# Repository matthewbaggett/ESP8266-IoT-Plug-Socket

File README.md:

ESP8266 IoT Plug Socket
=======================

This is a drop-in-replacement board for the STATUS Model RCS-K09 radio-controlled wallplug.
This allows you to insert an ESP8266 into a wallplug and use it as an Internet-of-Things controllable device.

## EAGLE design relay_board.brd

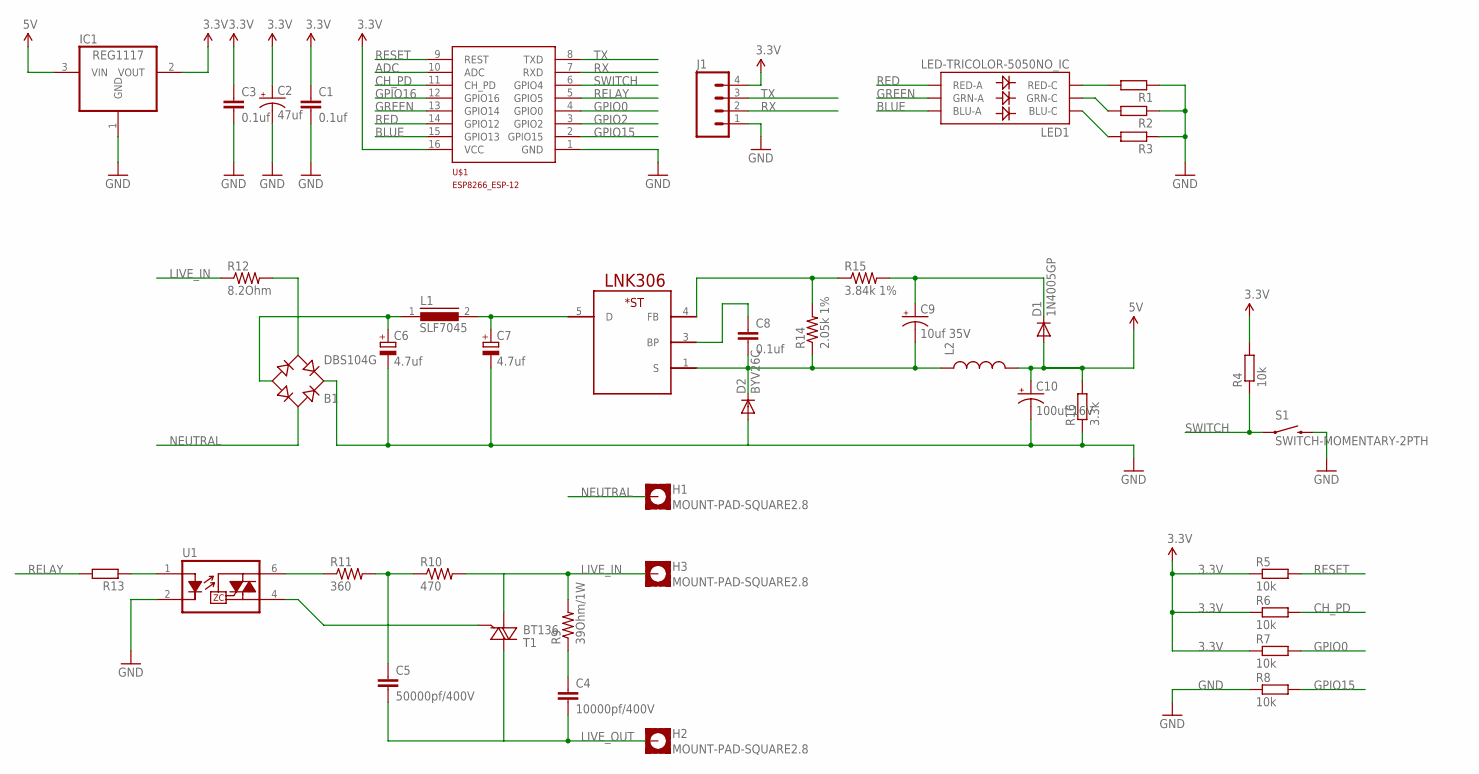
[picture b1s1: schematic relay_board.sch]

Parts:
B1: DBS104G; DBS
C1, C3: 0.1uf; 0805
C2: 47uf; PANASONIC_E
C4: 10000pf/400V; C050-045X075
C5: 50000pf/400V; C150-072X183
C6, C7: 4.7uf; E3,5-10
C8: 0.1uf; CAP-PTH-SMALL-KIT
C9: 10uf 35V; CPOL-RADIAL-10UF-25V-KIT
C10: 100uf 16V; CPOL-RADIAL-100UF-25V
D1: 1N4005GP; DO41-10
D2: BYV26C; SOD57-10
DA1: LNK306LNK306; LNK306_SMB
H1, H2, H3: MOUNT-PAD-SQUARE2.8; 2,8-PAD-SQUARE
IC1: REG1117; SOT223
J1: M04LOCK; 1X04_LOCK
L1: SLF7045
L2: INDUCTORDR1030; DR1030
LED1: LED-TRICOLOR-5050NO_IC; LED-TRICOLOR-5050
R1, R2, R3, R13: R-EU_M0805; M0805
R4: 10k; M0805
R5, R6, R7, R8: 10k; R0805
R9: 39Ohm/1W; AXIAL-0.6
R10: 470; AXIAL-0.4
R11: 360; AXIAL-0.4
R12: 8.2Ohm; AXIAL-0.6
R14: 2.05k 1%; 0805
R15: 3.84k 1%; 0805
R16: 3.3k; M0805
S1: SWITCH-MOMENTARY-2PTH; TACTILE-PTH
T1: BT136; TO220AB
U1: MOC3063S; DIP8SMD
U$1: ESP8266_ESP-12; ESP8266-ESP12

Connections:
3.3V: C1.1, C2.+, C3.1, IC1.2 (VOUT), J1.4, R4.2, R5.1, R6.1, R7.1, U$1.16 (VCC)
5V: C10.1 (+), D1.A, IC1.3 (VIN), L2.2, R16.2
ADC: U$1.10 (ADC)
BLUE: LED1.3 (BLU-A), U$1.15 (GPIO13)
CH_PD: R6.2, U$1.11 (CH_PD)
GND: B1.+, C1.2, C2.-, C3.2, C6.-, C7.-, C10.2 (-), D2.A, IC1.1 (GND), J1.1, R1.1, R2.1, R3.1, R8.1, R16.1, S1.3 (2), U1.2 (K), U$1.1 (GND)
GPIO0: R7.2, U$1.4 (GPIO0)
GPIO2: U$1.3 (GPIO2)
GPIO15: R8.2, U$1.2 (GPIO15)
GPIO16: U$1.12 (GPIO16)
GREEN: LED1.1 (GRN-A), U$1.13 (GPIO14)
LIVE_IN: H3.B2,8, R9.P$2 (2), R10.P$2 (2), R12.P$1 (1), T1.1 (A1)
LIVE_OUT: C4.2, C5.2, H2.B2,8, T1.2 (A2)
unnamed: LED1.5 (RED-C), R1.2
unnamed: LED1.6 (GRN-C), R2.2
unnamed: LED1.4 (BLU-C), R3.2
unnamed: R11.P$1 (1), U1.6 (T1)
unnamed: C4.1, R9.P$1 (1)
unnamed: C5.1, R10.P$1 (1), R11.P$2 (2)
unnamed: T1.3 (G), U1.4 (T2)
unnamed: C7.+, DA1.5 (D), L1.2
unnamed: B1.AC2, R12.P$2 (2)
unnamed: B1.-, C6.+, L1.1
unnamed: R13.1, U1.1 (A)
unnamed: C8.2, C9.2 (-), D2.C, DA1.1 (S), L2.1, R14.1
unnamed: C8.1, DA1.3 (BP)
unnamed: DA1.4 (FB), R14.2, R15.1
unnamed: C9.1 (+), D1.C, R15.2
NEUTRAL: B1.AC1, H1.B2,8
RED: LED1.2 (RED-A), U$1.14 (GPIO12)
RELAY: R13.2, U$1.5 (GPIO5)
RESET: R5.2, U$1.9 (REST)
RX: J1.2, U$1.7 (RXD)
SWITCH: R4.1, S1.1, U$1.6 (GPIO4)
TX: J1.3, U$1.8 (TXD)

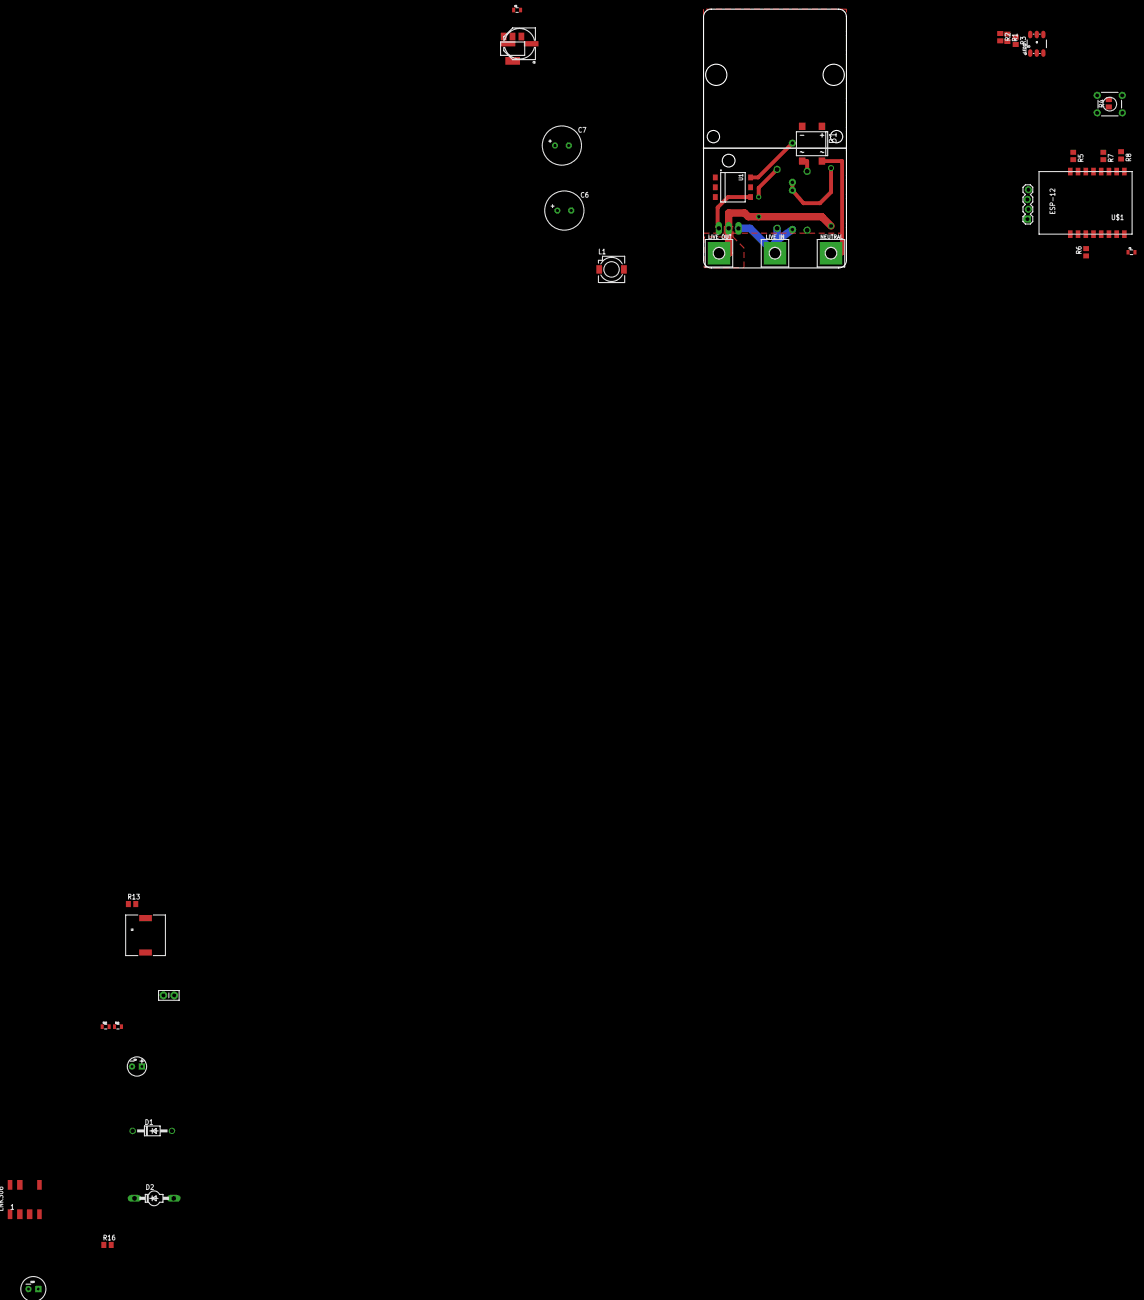
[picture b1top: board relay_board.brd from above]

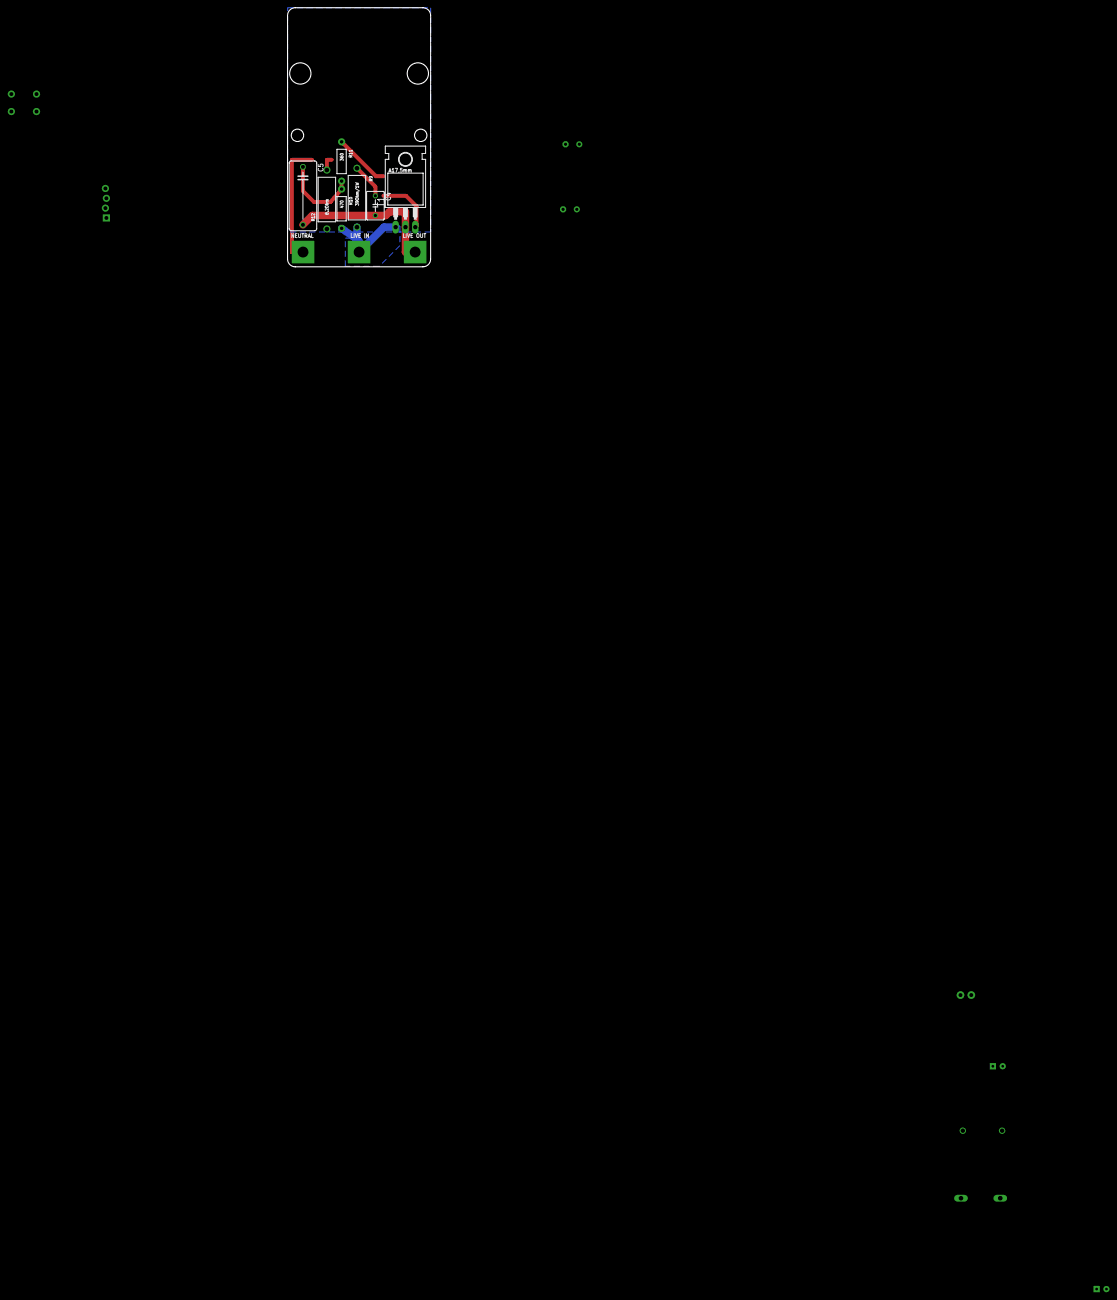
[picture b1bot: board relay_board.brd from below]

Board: 2 copper layers, 37.0 x 67.0 mm, 42 parts (7 on the bottom side), 32 nets.

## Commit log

2016-12-01 Initial version.

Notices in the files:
parts and their libraries:
SparkFun-Connectors: Licensing: Creative Commons ShareAlike 4.0 International - https://creativecommons.org/licenses/by-sa/4.0
SparkFun: Licensing: CC v3.0 Share-Alike You are welcome to use this library for commercial purposes.
